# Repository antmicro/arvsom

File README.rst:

=========================================
ARVSOM - Antmicro RISC-V System on Module
=========================================

Copyright (c) 2021 `Antmicro <https://www.antmicro.com>`_

.. image:: https://img.shields.io/badge/View%20on-Antmicro%20Open%20Source%20Portal-332d37?style=flat-square
      :target: https://opensource.antmicro.com/projects/arvsom

.. figure:: img/arvsom.png

Overview
--------

This repository contains open hardware design files for ARVSOM - Antmicro RISC-V System on Module (SoM) based on the StarFive 71x0 SoC.
The design is made in KiCad and currently in progress.

Repository structure
--------------------

The main repository directory contains KiCad PCB project files, a LICENSE and README.
The remaining files are stored in the following directories:

* ``lib`` - contains the component libraries
* ``img`` - contains graphics for this README

Key Features
------------

* StarFive 71x0 SoC (7100 in the current revision until 7110 becomes available)
* 2x DF40 board-to-board connectors for baseboard integration
* HDMI
* Gigabit Ethernet
* USB 3.0
* 2x MIPI CSI-2 (2 lanes each)
* I2C
* MIPI DSI (4 lanes)
* SD/SDIO/eMMC
* 26 GPIOs
* 32MB QSPI NOR Flash memory
* 8GB LPDDR4 (2x 4GB)

License
=======

`Apache-2.0 <LICENSE>`_

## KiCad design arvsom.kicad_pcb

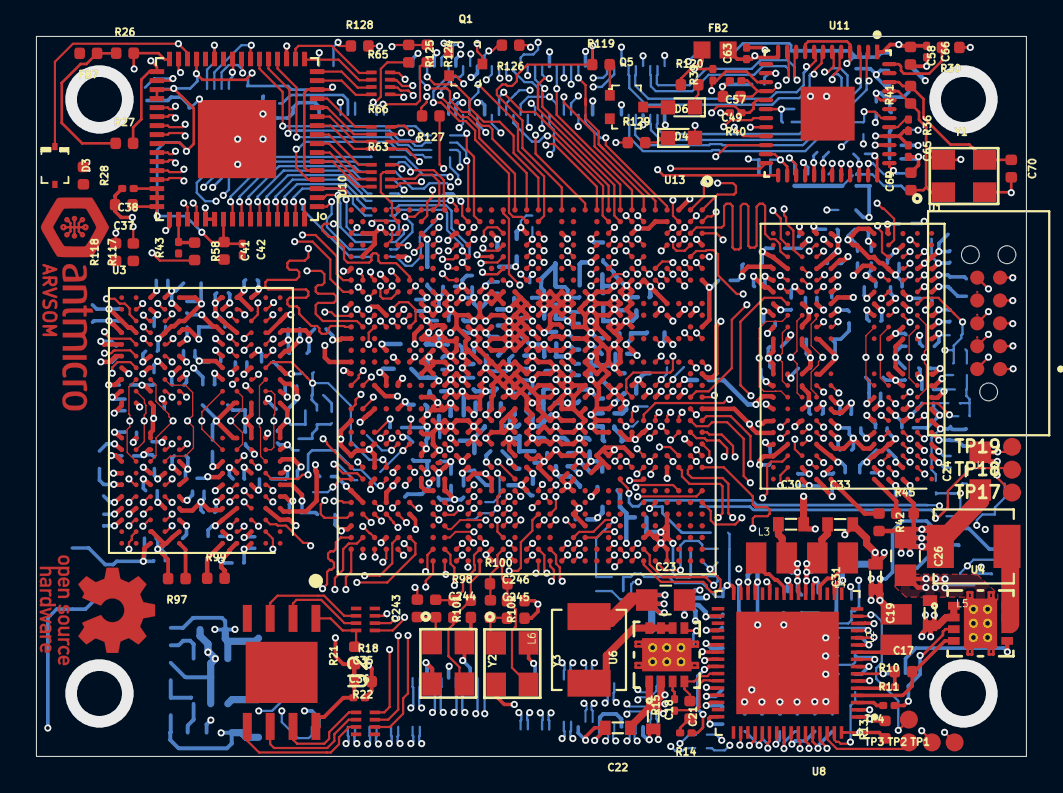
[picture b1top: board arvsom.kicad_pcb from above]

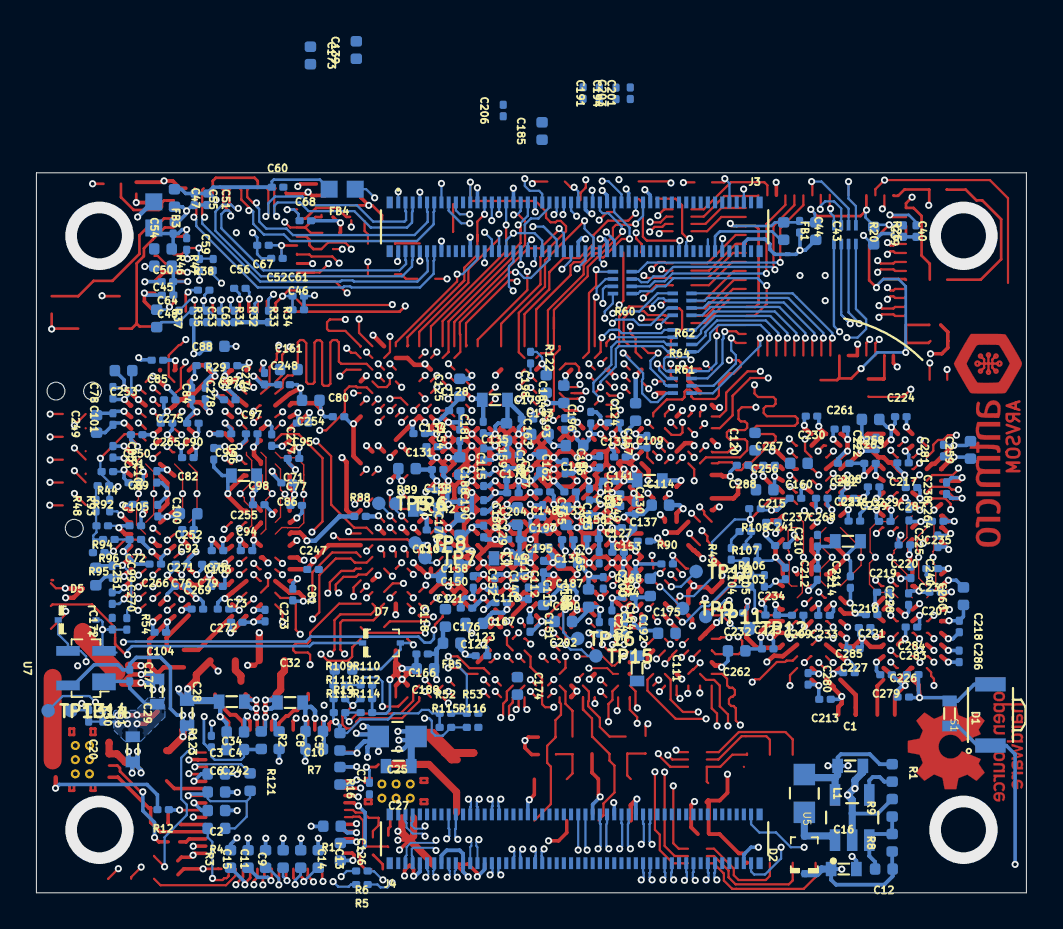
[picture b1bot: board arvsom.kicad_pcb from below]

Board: 12 copper layers, 55.0 x 40.0 mm, 451 parts (349 on the bottom side), 421 nets.

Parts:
C1, C16, C27, C28: C_10u_0603; 0603-cap
C2, C5, C7, C9, C15, C37, C39, C41, C43: C_2u2_0402; 0402-cap
C3, C4, C8, C114, C115, C118, C120, C121, C122, C139, C182, C184, C249, C251, C252, C253, C258, C259, C260, C262: C_10u_0402; 0402-cap
C6, C11, C14, C45, C47, C49, C50, C58: C_4u7_0402; 0402-cap
C10, C13, C17, C18, C242: C_100n_0402_16V; 0402-cap
C12: C_1n0_0402; 0402-cap
C19, C20, C21, C22, C29, C30, C31, C32, C33, C34, C109, C110, C111, C116, C135, C255, C257: C_22u_0603; 0603-cap
C23, C24, C25, C26: C_100u_0805; 0805-cap
C35, C108, C124, C125, C126, C143, C173, C174, C175, C183, C185, C186, C187, C189, C198, C199, C202, C254, C256: C_1u_0402; 0402-cap
C36, C38, C40, C42, C44, C54, C71, C72, C73, C74, C75, C76, C77, C78, C79, C80, C81, C82, C83, C84, C85, C86, C87, C88, C89, C90, C91, C92, C93, C94, C95, C96, C97, C98, C99, C100, C101, C102, C103, C104, C105, C106, C107, C112, C113, C117, C119, C123, C127, C128, C129, C130, C131, C132, C133, C134, C136, C137, C138, C140, C141, C142, C144, C145, C146, C147, C148, C149, C150, C151, C152, C153, C154, C155, C156, C157, C158, C159, C162, C164, C165, C166, C167, C168, C169, C171, C172, C176, C177, C178, C179, C180, C181, C188, C190, C191, C192, C193, C194, C195, C196, C197, C200, C201, C203, C204, C205, C206, C207, C208, C209, C210, C211, C212, C213, C214, C215, C216, C217, C218, C219, C220, C221, C222, C223, C224, C225, C226, C227, C228, C229, C230, C231, C232, C233, C234, C235, C236, C237, C238, C239, C240, C241, C247, C248, C250, C261, C263, C264, C265, C266, C267, C268, C269, C270, C271, C272, C273, C274, C275, C276, C277, C278, C279, C280, C281, C282, C283, C284, C285, C286, C287, C288: C_100n_0201; 0201-res
C46, C48, C51, C52, C53: C_470n_0201; 0201-res
C55, C56, C57, C59, C60, C61, C62, C63, C64, C65, C66, C67, C68: C_10n_0201; 0201-res
C69, C70: C_22p_0402; 0402-cap
C160, C161, C163, C170: C_1n_0402; 0402-res
C243, C244, C245, C246: C_10p_0402; 0402-cap
D1: PGB1010603MR
D2, D3, D5, D7: PMEG3010CEJ; SOD-323F
D4, D6: KP-1608CGCK; LED_0603
FB1, FB5, FB6, FB7: BLM15PD121SN1D; 0402-res
FB2, FB3, FB4: BLM18AG601SN1D; 0603
J1: TAG-10PIN; Tag-Connect_TC2050-IDC-NL
J3, J4: DF40C-100DP-0.4V(51); HRS_DF40C-100DP-0.4V(51)
L1: 10uH; 0805-res
L2, L3, L4: 1uH_2.0x1.6; INDC2016X100N
L5: 0.56uH_7.3A; SRP4020
L6: 0.47uH_10.5A; SRP4020
N1: antmicro_logo; antmicro-logo_scaled_12mm
N2: oshw_logo; oshw-logo
Q1: DMG1013UWQ-7; SOT-323
Q5: DMG1012UW; SOT-323
R1, R98, R100: R_1M0_0402; 0402-res
R2, R3, R4: R_10k_0402; 0402-res
R5, R6, R10, R11, R12, R14, R15, R16, R46, R47, R48, R123: R_0R_0201; 0201-res
R7: R_2k2_0402; 0402-res
R8: R_49k9_0402; 0402-res
R9: R_13k3_0402; 0402-res
R13, R30: R_12k1_0402; 0402-res
R17, R21, R117, R118, R124, R125: R_4k7_0402; 0402-res
R18, R20, R22, R60, R61, R62, R63, R64, R65, R66: 4x33R_0201_array; EXB18V
R19, R26, R27, R29, R37, R120, R121, R129: R_1k_0402; 0402-res
R25, R31, R32, R33, R34, R35, R36, R38, R39, R40, R43, R44, R49, R50, R51, R52, R53, R54, R88, R90, R92, R93, R94, R95, R96, R103, R104, R105, R106, R107, R108, R109, R110, R111, R112, R113, R114, R115, R116, R122: R_10k_0201; 0201-res
R28: R_27k_0402; 0402-res
R41: R_1M5_0402; 0402-res
R42, R45, R89, R91, R97, R99: R_240R_0402; 0402-res
R58, R119, R128: R_33R_0402; 0402-res
R101, R102: R_0R_0402; 0402-res
R126, R127: R_100k_0402; 0402-res
S1: B3U-3000PM; B3U-3000P
TP1, TP2, TP3, TP4, TP17, TP18, TP19: TP_SMD1MM; Testpoint_smd_1mm
TP5, TP6, TP7, TP8, TP9, TP10, TP11, TP12, TP13, TP14, TP15, TP16: TP_SMD_0_75MM; Testpoint_smd_0_75mm
U1, U3: MT53D1024M32D4DT-053; BGA-200_10.0x14.5mm_Layout12x22_P0.80x0.65mm
U2: GD25LQ256DWIGR; GD25Q16CWIG
U4, U6: CSD86330Q3D
U5: LMR62014XMF_NOPB; SOT95P280X145-5N
U7: STM811RW16F; SOT-143-4
U8: TPS65086100; S-PVQFN-N64
U10: TDA19988BHN_C1,557; QFN50P900X900X100-65N
U11: KSZ9031RNXCA; QFN-48-Microchip-QFN77-48LD-PL-2
U13: VIC7100; vic7100
Y1, Y2: ABM8G-25.000MHZ-18-D2Y-T; KX-7
Y3: ABM8G-27.000MHZ-18-D2Y-T; KX-7

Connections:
5V0_IN: J3.77, J3.79, J3.81, J3.83, J3.85, J3.87
/Ethernet/AVDDH: C58.1, C63.1, C66.1, FB2.2, U11.1, U11.12
/Ethernet/AVDDL: C47.1, C51.1, C55.1, C60.1, FB4.2, U11.4, U11.9
/Ethernet/AVDDL_PLL: C50.1, C54.1, C59.1, FB3.2, U11.44
/Ethernet/ETH_RESETn: R46.2, R47.2, U11.42
/PMIC/U5FB: C12.2, R8.2, R9.1, U5.3
/VIC7100 config/ATEMP_TEST0: R51.1, TP13.1, U13.U25
/VIC7100 config/ATEMP_TEST1: R50.1, TP14.1, U13.U24
/VIC7100 config/ATEMP_VCAL: TP16.1, U13.V24
/VIC7100 config/ATEMP_VSS: TP15.1, U13.V25
AVDD3V3_USB: C202.1, C205.1, FB6.1, U13.AA23
AVDD09_PLL: C108.1, C113.1, C119.1, C123.1, FB5.1, U13.U21, U13.U22, U13.V21
BOOT_FROM_UARTn: J3.93, R128.1
BOOT_MODE: R115.2, R116.1, U13.M28
BOOT_SEL0: R109.2, R110.1, U13.E31
BOOT_SEL1: R111.2, R112.1, U13.F31
BOOT_SEL2: Q1.3, R113.2, R114.1, U13.F30
CDTX_DSI_CK_N: J4.69, U13.J30
CDTX_DSI_CK_P: J4.71, U13.J31
CDTX_DSI_D0_N: J4.57, U13.G30
CDTX_DSI_D0_P: J4.59, U13.G31
CDTX_DSI_D1_N: J4.63, U13.H30
CDTX_DSI_D1_P: J4.65, U13.H31
CLK_25M_IN: R98.1, R101.1, U13.Y30
CLK_25M_OUT: C244.1, R98.2, U13.Y31, Y2.3
CLK_27M_IN: R100.1, R102.1, U13.V30
CLK_27M_OUT: C246.1, R100.2, U13.V31, Y3.3
CSI0_PWDN: J3.97, U13.V6
CSI1RX_CLK_N: J4.40, U13.M30
CSI1RX_CLK_P: J4.42, U13.M31
CSI1RX_D0_N: J4.28, U13.P30
CSI1RX_D0_P: J4.30, U13.P31
CSI1RX_D1_N: J4.34, U13.N30
CSI1RX_D1_P: J4.36, U13.N31
CSI2RX_CLK_N: J4.27, U13.U30
CSI2RX_CLK_P: J4.29, U13.U31
CSI2RX_D0_N: J4.15, U13.T30
CSI2RX_D0_P: J4.17, U13.T31
CSI2RX_D1_N: J4.21, U13.R30
CSI2RX_D1_P: J4.23, U13.R31
CTL5: D1.2, J3.92, R4.2, S1.1, U8.63
DDR0_A00: U1.H2, U1.R2, U13.C10
DDR0_A01: U1.J2, U1.P2, U13.B10
DDR0_A02: U1.H9, U1.R9, U13.A15
DDR0_A03: U1.H10, U1.R10, U13.D10
DDR0_A04: U1.H11, U1.R11, U13.D12
DDR0_A05: U1.J11, U1.P11, U13.E10
DDR0_CK0_N: U1.J9, U13.B14
DDR0_CK0_P: U1.J8, U13.A14
DDR0_CK1_N: U1.P9, U13.B12
DDR0_CK1_P: U1.P8, U13.A12
DDR0_CKE0: U1.J4, U1.P4, U13.C17
DDR0_CKE1: U1.J5, U1.P5, U13.F17
DDR0_CS0: U1.H4, U13.F19
DDR0_CS1: U1.H3, U13.A17
DDR0_CS2: U1.R4, U13.B17
DDR0_CS3: U1.R3, U13.E14
DDR0_DMI0: U1.C3, U13.E22
DDR0_DMI1: U1.C10, U13.C19
DDR0_DMI2: U1.Y3, U13.D6
DDR0_DMI3: U1.Y10, U13.D4
DDR0_DQ00: U1.B2, U13.F23
DDR0_DQ01: U1.C2, U13.E23
DDR0_DQ02: U1.E2, U13.D22
DDR0_DQ03: U1.F2, U13.F22
DDR0_DQ04: U1.F4, U13.C22
DDR0_DQ05: U1.E4, U13.B22
DDR0_DQ06: U1.C4, U13.A23
DDR0_DQ07: U1.B4, U13.A22
DDR0_DQ08: U1.B11, U13.A21
DDR0_DQ09: U1.C11, U13.C20
DDR0_DQ10: U1.E11, U13.E20
DDR0_DQ11: U1.F11, U13.D20
DDR0_DQ12: U1.F9, U13.E19
DDR0_DQ13: U1.E9, U13.D19
DDR0_DQ14: U1.C9, U13.B19
DDR0_DQ15: U1.B9, U13.A19
DDR0_DQ16: U1.AA2, U13.A5
DDR0_DQ17: U1.Y2, U13.D7
DDR0_DQ18: U1.V2, U13.C7
DDR0_DQ19: U1.U2, U13.E7
DDR0_DQ20: U1.U4, U13.B5
DDR0_DQ21: U1.V4, U13.C6
DDR0_DQ22: U1.Y4, U13.E6
DDR0_DQ23: U1.AA4, U13.B4
DDR0_DQ24: U1.AA11, U13.A2
DDR0_DQ25: U1.Y11, U13.B3
DDR0_DQ26: U1.V11, U13.A3
DDR0_DQ27: U1.U11, U13.C4
DDR0_DQ28: U1.U9, U13.B2
DDR0_DQ29: U1.V9, U13.B1
DDR0_DQ30: U1.Y9, U13.A1
DDR0_DQ31: U1.AA9, U13.C2
DDR0_DQS0N: U1.E3, U13.C23
DDR0_DQS0P: U1.D3, U13.B23
DDR0_DQS1N: U1.E10, U13.A20
DDR0_DQS1P: U1.D10, U13.B20
DDR0_DQS2N: U1.V3, U13.B6
DDR0_DQS2P: U1.W3, U13.A6
DDR0_DQS3N: U1.V10, U13.C3
DDR0_DQS3P: U1.W10, U13.D3
DDR0_ODT0: R95.1, U1.G2, U13.D17
DDR0_ODT1: R44.2, R92.1, R93.2, U1.T2, U13.G17
DDR0_ODT_0: R48.1, R94.2, R95.2, R96.2
DDR0_ODT_1: R48.2, R92.2
DDR0_PLL_REFOUT_N: TP5.1, U13.D16
DDR0_PLL_REFOUT_P: TP6.1, U13.E16
DDR0_PLL_TESTOUT_N: TP7.1, U13.H19
DDR0_PLL_TESTOUT_P: TP8.1, U13.G19
DDR0_RSTN: U1.T11, U13.B18
DDR1_A00: U3.H2, U3.R2, U13.AG16
DDR1_A01: U3.J2, U3.P2, U13.AJ18
DDR1_A02: U3.H9, U3.R9, U13.AJ16
DDR1_A03: U3.H10, U3.R10, U13.AF14
DDR1_A04: U3.H11, U3.R11, U13.AL14
DDR1_A05: U3.J11, U3.P11, U13.AG14
DDR1_CK0_N: U3.J9, U13.AK18
DDR1_CK0_P: U3.J8, U13.AL18
DDR1_CK1_N: U3.P9, U13.AK16
DDR1_CK1_P: U3.P8, U13.AL16
DDR1_CKE0: U3.J4, U3.P4, U13.AG23
DDR1_CKE1: U3.J5, U3.P5, U13.AJ24
DDR1_CS0: U3.H4, U13.AK23
DDR1_CS1: U3.H3, U13.AH21
DDR1_CS2: U3.R4, U13.AH20
DDR1_CS3: U3.R3, U13.AF20
DDR1_DMI0: U3.C3, U13.AG30
DDR1_DMI1: U3.C10, U13.AJ26
DDR1_DMI2: U3.Y3, U13.AG11
DDR1_DMI3: U3.Y10, U13.AH8
DDR1_DQ00: U3.B2, U13.AF29
DDR1_DQ01: U3.C2, U13.AG29
DDR1_DQ02: U3.E2, U13.AH30
DDR1_DQ03: U3.F2, U13.AF30
DDR1_DQ04: U3.F4, U13.AJ29
DDR1_DQ05: U3.E4, U13.AK29
DDR1_DQ06: U3.C4, U13.AL30
DDR1_DQ07: U3.B4, U13.AL29
DDR1_DQ08: U3.B11, U13.AF26
DDR1_DQ09: U3.C11, U13.AH27
DDR1_DQ10: U3.E11, U13.AG27
DDR1_DQ11: U3.F11, U13.AG26
DDR1_DQ12: U3.F9, U13.AL27
DDR1_DQ13: U3.E9, U13.AL26
DDR1_DQ14: U3.C9, U13.AF24
DDR1_DQ15: U3.B9, U13.AF23
DDR1_DQ16: U3.AA2, U13.AL11
DDR1_DQ17: U3.Y2, U13.AK11
DDR1_DQ18: U3.V2, U13.AL10
DDR1_DQ19: U3.U2, U13.AJ11
DDR1_DQ20: U3.U4, U13.AG10
DDR1_DQ21: U3.V4, U13.AH11
DDR1_DQ22: U3.Y4, U13.AF11
DDR1_DQ23: U3.AA4, U13.AF10
DDR1_DQ24: U3.AA11, U13.AL8
DDR1_DQ25: U3.Y11, U13.AL7
DDR1_DQ26: U3.V11, U13.AK8
DDR1_DQ27: U3.U11, U13.AJ8
DDR1_DQ28: U3.U9, U13.AF8
DDR1_DQ29: U3.V9, U13.AG8
DDR1_DQ30: U3.Y9, U13.AG7
DDR1_DQ31: U3.AA9, U13.AF7
DDR1_DQS0N: U3.E3, U13.AJ30
DDR1_DQS0P: U3.D3, U13.AK30
DDR1_DQS1N: U3.E10, U13.AK27
DDR1_DQS1P: U3.D10, U13.AJ27
DDR1_DQS2N: U3.V3, U13.AJ10
DDR1_DQS2P: U3.W3, U13.AK10
DDR1_DQS3N: U3.V10, U13.AK7
DDR1_DQS3P: U3.W10, U13.AJ7
DDR1_ODT0: R104.1, U3.G2, U13.AH24
DDR1_ODT1: R106.2, R107.1, R108.2, U3.T2, U13.AH23
DDR1_ODT_0: R49.1, R103.2, R104.2, R105.2
DDR1_ODT_1: R49.2, R107.2
DDR1_PLL_REFOUT_N: TP9.1, U13.AF21
DDR1_PLL_REFOUT_P: TP10.1, U13.AG21
DDR1_PLL_TESTOUT_N: TP11.1, U13.AK24
DDR1_PLL_TESTOUT_P: TP12.1, U13.AL24
DDR1_RSTN: U3.T11, U13.AL23
ETH0_N: J3.10, U11.3
ETH0_P: J3.12, U11.2
ETH1_N: J3.6, U11.6
ETH1_P: J3.4, U11.5
ETH2_N: J3.9, U11.8
ETH2_P: J3.11, U11.7
ETH3_N: J3.5, U11.11
ETH3_P: J3.3, U11.10
ETH_LED1: J3.17, R40.1, U11.17
ETH_LED2: J3.15, R39.1, U11.15
GND: C1.2, C2.1, C3.2, C4.2, C5.1, C6.2, C7.1, C8.2, C9.2, C10.2, C11.2, C13.1, C14.1, C15.2, C16.2, C19.2, C20.2, C21.2, C22.2, C23.2, C24.2, C25.2, C26.2, C27.2, C28.2, C29.2, C30.2, C31.2, C32.2, C33.2, C34.2, C35.2, C36.2, C37.2, C38.2, C39.2, C40.2, C41.2, C42.2, C43.2, C44.2, C45.2, C46.2, C47.2, C48.2, C49.2, C50.2, C51.2, C52.2, C53.2, C54.2, C55.2, C56.2, C57.2, C58.2, C59.2, C60.2, C61.2, C62.2, C63.2, C64.2, C65.2, C66.2, C67.2, C68.2, C69.2, C70.2, C71.2, C72.2, C73.2, C74.2, C75.2, C76.2, C77.2, C78.2, C79.2, C80.2, C81.2, C82.2, C83.2, C84.2, C85.2, C86.2, C87.2, C88.2, C89.2, C90.2, C91.2, C92.2, C93.2, C94.2, C95.2, C96.2, C97.2, C98.2, C99.2, C100.2, C101.2, C102.2, C103.2, C104.2, C105.2, C106.2, C107.2, C108.2, C109.2, C110.2, C111.2, C112.2, C113.2, C114.2, C115.2, C116.2, C117.2, C118.2, C119.2, C120.2, C121.2, C122.2, C123.2, C124.2, C125.2, C126.2, C127.2, C128.2, C129.2, C130.2, C131.2, C132.2, C133.2, C134.2, C135.2, C136.2, C137.2, C138.2, C139.2, C140.2, C141.2, C142.2, C143.2, C144.2, C145.2, C146.2, C147.2, C148.2, C149.2, C150.2, C151.2, C152.2, C153.2, C154.2, C155.2, C156.2, C157.2, C158.2, C159.2, C160.2, C161.2, C162.2, C163.2, C164.2, C165.2, C166.2, C167.2, C168.2, C169.2, C170.2, C171.2, C172.2, C173.2, C174.2, C175.2, C176.2, C177.2, C178.2, C179.2, C180.2, C181.2, C182.2, C183.2, C184.2, C185.2, C186.2, C187.2, C188.2, C189.2, C190.2, C191.2, C192.2, C193.2, C194.2, C195.2, C196.2, C197.2, C198.2, C199.2, C200.2, C201.2, C202.2, C203.2, C204.2, C205.2, C206.2, C207.2, C208.2, C209.2, C210.2, C211.2, C212.2, C213.2, C214.2, C215.2, C216.2, C217.2, C218.2, C219.2, C220.2, C221.2, C222.2, C223.2, C224.2, C225.2, C226.2, C227.2, C228.2, C229.2, C230.2, C231.2, C232.2, C233.2, C234.2, C235.2, C236.2, C237.2, C238.2, C239.2, C240.2, C241.2, C242.2, C243.2, C244.2, C245.2, C246.2, C247.2, C248.2, C249.2, C250.2, C251.2, C252.2, C253.2, C254.2, C255.2, C256.2, C257.2, C258.2, C259.2, C260.2, C261.2, C262.2, C263.2, C264.2, C265.2, C266.2, C267.2, C268.2, C269.2, C270.2, C271.2, C272.2, C273.2, C274.2, C275.2, C276.2, C277.2, C278.2, C279.2, C280.2, C281.2, C282.2, C283.2, C284.2, C285.2, C286.2, C287.2, C288.2, D1.1, D6.2, J1.3, J1.5, J1.9, J3.1, J3.2, J3.7, J3.8, J3.13, J3.14, J3.22, J3.23, J3.32, J3.33, J3.42, J3.43, J3.52, J3.53, J3.59, J3.60, J3.65, J3.66, J3.71, J3.74, J3.98, J4.7, J4.8, J4.13, J4.14, J4.19, J4.20, J4.25, J4.26, J4.31, J4.32, J4.37, J4.38, J4.44, J4.50, J4.55, J4.56, J4.61, J4.62, J4.67, J4.68, J4.73, J4.74, J4.79, J4.80, J4.85, J4.86, J4.91, J4.92, J4.97, J4.98, Q5.2, R3.2, R7.2, R9.2, R13.2, R17.2, R25.1, R29.2, R30.1, R50.2, R51.2, R53.2, R89.1, R91.1, R93.1, R96.1, R105.1, R108.1, R110.2, R112.2, R114.2, R116.2, R122.1, S1.2, TP19.1, U1.A3, U1.A10, U1.AB3, U1.AB5, U1.AB8, U1.AB10, U1.C1, U1.C5, U1.C8, U1.C12, U1.D2, U1.D4, U1.D9, U1.D11, U1.E1, U1.E5, U1.E8, U1.E12, U1.G1, U1.G3, U1.G5, U1.G8, U1.G10, U1.G12, U1.J1, U1.J3, U1.J10, U1.J12, U1.K2, U1.K4, U1.K9, U1.K11, U1.N2, U1.N4, U1.N9, U1.N11, U1.P1, U1.P3, U1.P10, U1.P12, U1.T1, U1.T3, U1.T5, U1.T8, U1.T10, U1.T12, U1.V1, U1.V5, U1.V8, U1.V12, U1.W2, U1.W4, U1.W9, U1.W11, U1.Y1, U1.Y5, U1.Y8, U1.Y12, U2.4, U3.A3, U3.A10, U3.AB3, U3.AB5, U3.AB8, U3.AB10, U3.C1, U3.C5, U3.C8, U3.C12, U3.D2, U3.D4, U3.D9, U3.D11, U3.E1, U3.E5, U3.E8, U3.E12, U3.G1, U3.G3, U3.G5, U3.G8, U3.G10, U3.G12, U3.J1, U3.J3, U3.J10, U3.J12, U3.K2, U3.K4, U3.K9, U3.K11, U3.N2, U3.N4, U3.N9, U3.N11, U3.P1, U3.P3, U3.P10, U3.P12, U3.T1, U3.T3, U3.T5, U3.T8, U3.T10, U3.T12, U3.V1, U3.V5, U3.V8, U3.V12, U3.W2, U3.W4, U3.W9, U3.W11, U3.Y1, U3.Y5, U3.Y8, U3.Y12, U4.9, U5.2, U6.9, U7.1, U8.1, U8.6, U8.14, U8.18, U8.29, U8.30, U8.34, U8.36, U8.40, U8.48, U8.50, U8.52, U8.61, U8.65, U10.19, U10.49, U10.53, U10.54, U10.65, U11.29, U11.49, U13.A4, U13.A7, U13.A11, U13.A18, U13.AA8, U13.AA10, U13.AA12, U13.AA13, U13.AA14, U13.AA15, U13.AA17, U13.AA19, U13.AA20, U13.AA22, U13.AA24, U13.AA29, U13.AB3, U13.AB8, U13.AB10, U13.AB11, U13.AB17, U13.AB19, U13.AB20, U13.AB22, U13.AC8, U13.AC9, U13.AC10, U13.AC14, U13.AC15, U13.AC17, U13.AC19, U13.AC20, U13.AC22, U13.AC24, U13.AC25, U13.AD13, U13.AD14, U13.AD15, U13.AD19, U13.AD20, U13.AD21, U13.AD22, U13.AD25, U13.AD28, U13.AD29, U13.AE3, U13.AE8, U13.AE11, U13.AE14, U13.AE15, U13.AE20, U13.AE23, U13.AE24, U13.AE31, U13.AF27, U13.AG5, U13.AG18, U13.AG24, U13.AH3, U13.AH7, U13.AH10, U13.AH13, U13.AH16, U13.AH26, U13.AH29, U13.AJ21, U13.AJ23, U13.AK3, U13.AK5, U13.AK26, U13.AL6, U13.AL9, U13.AL12, U13.AL15, U13.AL19, U13.AL22, U13.AL25, U13.AL28, U13.B21, U13.C1, U13.D2, U13.D9, U13.D23, U13.D27, U13.D28, U13.D29, U13.D30, U13.D31, U13.E2, U13.E17, U13.E29, U13.E30, U13.F7, U13.F16, U13.F20, U13.F24, U13.F29, U13.G3, U13.G13, U13.G16, U13.G20, U13.G22, U13.H7, U13.H9, U13.H10, U13.H16, U13.H17, U13.H18, U13.H20, U13.J9, U13.J10, U13.J12, U13.J16, U13.J17, U13.J22, U13.J23, U13.K3, U13.K5, U13.K8, U13.K9, U13.K10, U13.K11, U13.K22, U13.K23, U13.K25, U13.L8, U13.L9, U13.L10, U13.L11, U13.L12, U13.L13, U13.L16, U13.L18, U13.L19, U13.L20, U13.L22, U13.L23, U13.L28, U13.M10, U13.M11, U13.M12, U13.M13, U13.M14, U13.M15, U13.M16, U13.M17, U13.M18, U13.M20, U13.M22, U13.M24, U13.M25, U13.M26, U13.M27, U13.N3, U13.N12, U13.N15, U13.N16, U13.N17, U13.N18, U13.N20, U13.N22, U13.N24, U13.N25, U13.P12, U13.P14, U13.P15, U13.P18, U13.P20, U13.P22, U13.P24, U13.R12, U13.R14, U13.R15, U13.R20, U13.R22, U13.R23, U13.T3, U13.T9, U13.T10, U13.T11, U13.T12, U13.T14, U13.T22, U13.T24, U13.T25, U13.U8, U13.U9, U13.U10, U13.U11, U13.U12, U13.U13, U13.U18, U13.U19, U13.U20, U13.U23, U13.V10, U13.V11, U13.V12, U13.V13, U13.V18, U13.V19, U13.V20, U13.W3, U13.W10, U13.W12, U13.W13, U13.W20, U13.W21, U13.W24, U13.W25, U13.W30, U13.W31, U13.Y8, U13.Y9, U13.Y10, U13.Y14, U13.Y16, U13.Y17, U13.Y18, U13.Y19, U13.Y20, Y1.2, Y1.4, Y2.2, Y2.4, Y3.2, Y3.4
GP43_LED: J3.21, R119.1, U13.N1
GPIO0: J3.25, U13.E1
GPIO1: J3.24, U13.D1
GPIO2: J3.27, U13.F2
GPIO3: J3.26, U13.G2
GPIO4: J3.29, U13.G6
GPIO5: J3.28, U13.F6
GPIO6: J3.30, U13.F1
GPIO7: J3.31, U13.G1
GPIO8: J3.34, U13.J7
GPIO9: J3.36, U13.G5
GPIO10: J3.35, U13.H2
GPIO11: J3.37, U13.H1
GPIO12: J3.38, U13.F5
GPIO13: J3.51, R126.2, U13.K7
GPIO14: J3.55, U13.J4
GPIO15: J3.39, U13.J3
GPIO16: J3.40, U13.J6
GPIO17: J3.41, U13.F4
GPIO18: J3.44, U13.J2
GPIO19: J3.45, U13.K4
GPIO20: J3.46, U13.G4
GPIO21: J3.47, U13.K6
GPIO22: J3.48, U13.J1
GPIO44: J3.50, U13.R5
GPIO45: J3.49, U13.R4
GPIO46: J3.54, U13.R3
GPIO47: J3.56, U13.R2
GPIO48: J3.58, U13.T7
GPIO55_GMAC_RESETN: R122.2, U13.T4
GPIO63_GMAC_RESETN: R47.1, U13.V7
HDMI_1V8: C37.1, C38.1, C39.1, C40.1, C41.1, C42.1, C43.1, C44.1, FB1.1, U10.5, U10.14, U10.29, U10.35, U10.36, U10.41, U10.46, U10.47, U10.48, U10.55
HDMI_12MHZ: R20.1, U10.27
HDMI_BCLK: R20.2, U10.23
HDMI_CEC: D3.K, J4.51, U10.30
HDMI_DSCL: J4.100, R27.2, U10.33
HDMI_DSDA: J4.99, R26.2, U10.32
HDMI_HPD: J4.53, U10.31
HDMI_I2S_TX0: R20.4, U10.25
HDMI_INT: R43.2, R58.1, U10.50
HDMI_LRCLK: R20.3, U10.24
HDMI_SWING: R25.2, U10.34
HDMI_TX0_N: J4.84, U10.39
HDMI_TX0_P: J4.82, U10.40
HDMI_TX1_N: J4.78, U10.42
HDMI_TX1_P: J4.76, U10.43
HDMI_TX2_N: J4.72, U10.44
HDMI_TX2_P: J4.70, U10.45
HDMI_TXC_N: J4.90, U10.37
HDMI_TXC_P: J4.88, U10.38
I2C0_SCL: R5.1, R117.2, U10.52, U13.W5
I2C0_SDA: R6.1, R118.2, U10.51, U13.V4
I2C2_SCL: J3.80, R124.2, U13.V3
I2C2_SDA: J3.82, R125.2, U13.V5
JTAG_TCK: J1.4, U13.H22
JTAG_TDI: J1.8, U13.C25
JTAG_TDO: J1.6, U13.A25
JTAG_TMS: J1.2, U13.A26
JTAG_TRSTN: J1.10, U13.G23
LCD_DATA0: R61.1, U10.63
LCD_DATA1: R61.2, U10.62
LCD_DATA2: R61.3, U10.61
LCD_DATA3: R61.4, U10.60
LCD_DATA4: R62.1, U10.59
LCD_DATA5: R62.2, U10.58
LCD_DATA6: R62.3, U10.57
LCD_DATA7: R62.4, U10.56
LCD_DATA8: R63.1, U10.9
LCD_DATA9: R63.2, U10.8
LCD_DATA10: R63.3, U10.7
LCD_DATA11: R63.4, U10.6
LCD_DATA12: R64.8, U10.3
LCD_DATA13: R64.7, U10.2
LCD_DATA14: R64.6, U10.1
LCD_DATA15: R64.5, U10.64
LCD_DATA16: R65.1, U10.18
LCD_DATA17: R65.2, U10.17
LCD_DATA18: R65.3, U10.16
LCD_DATA19: R65.4, U10.15
LCD_DATA20: R66.1, U10.13
LCD_DATA21: R66.2, U10.12
LCD_DATA22: R66.3, U10.11
LCD_DATA23: R66.4, U10.10
LCD_DE: R60.2, U10.20
LCD_HSYNC: R60.4, U10.22
LCD_PCLK: R60.1, U10.4
LCD_VSYNC: R60.3, U10.21
LDO_3V3: C6.1, R4.1, R121.2, U8.9
LED_MODE: R36.1, U11.41
unnamed: C11.1, U8.56
unnamed: C13.2, U8.53
unnamed: C14.2, U8.54
unnamed: C17.1, R10.2
unnamed: C17.2, U4.4, U8.4
unnamed: C18.1, R14.2
unnamed: C18.2, U6.4, U8.42
unnamed: C69.1, R41.1, U11.45, Y1.1
unnamed: C70.1, R41.2, U11.46, Y1.3
unnamed: C243.1, R101.2, Y2.1
unnamed: C245.1, R102.2, Y3.1
unnamed: D2.A, L1.2, U5.1
unnamed: D3.A, R28.1
unnamed: D4.1, R120.2
unnamed: D4.2, Q5.3
unnamed: D6.1, R129.2
unnamed: D7.K, TP18.1
unnamed: FB7.1, R26.1, R27.1
unnamed: L2.1, U8.10
unnamed: L3.1, U8.25
unnamed: L4.1, U8.20
unnamed: L5.1, U4.6, U4.7, U4.8
unnamed: L6.1, U6.6, U6.7, U6.8
unnamed: Q1.1, R127.2, R128.2
unnamed: Q5.1, R119.2
unnamed: R1.2, U5.4
unnamed: R5.2, TP1.1, U8.58
unnamed: R6.2, TP2.1, U8.59
unnamed: R10.1, U8.5
unnamed: R11.1, U8.3
unnamed: R11.2, U4.3
unnamed: R12.1, U8.7
unnamed: R12.2, U4.5
unnamed: R13.1, U8.64
unnamed: R14.1, U8.41
unnamed: R15.1, U8.43
unnamed: R15.2, U6.3
unnamed: R16.1, U8.39
unnamed: R16.2, U6.5
unnamed: R17.1, U8.45
unnamed: R18.6, U2.3
unnamed: R18.7, U2.2
unnamed: R18.8, R21.2, U2.1
unnamed: R20.5, U13.M6
unnamed: R20.6, U13.K1
unnamed: R20.7, U13.L1
unnamed: R20.8, U13.H4
unnamed: R22.1, U2.7
unnamed: R22.2, U2.6
unnamed: R22.3, U2.5
unnamed: R30.2, U11.48
unnamed: R42.1, U1.A8
unnamed: R45.1, U1.A5
unnamed: R58.2, U13.M5
unnamed: R60.5, U13.Y2
unnamed: R60.6, U13.AA1
unnamed: R60.7, U13.AA4
unnamed: R60.8, U13.AA3
unnamed: R61.5, U13.AA2
unnamed: R61.6, U13.AB1
unnamed: R61.7, U13.AA6
unnamed: R61.8, U13.AA5
unnamed: R62.5, U13.AB2
unnamed: R62.6, U13.AC1
unnamed: R62.7, U13.AB6
unnamed: R62.8, U13.AB5
unnamed: R63.5, U13.AB4
unnamed: R63.6, U13.AD1
unnamed: R63.7, U13.AG2
unnamed: R63.8, U13.AB7
unnamed: R64.1, U13.AH2
unnamed: R64.2, U13.AG3
unnamed: R64.3, U13.AE1
unnamed: R64.4, U13.AD2
unnamed: R65.5, U13.AE2
unnamed: R65.6, U13.AD3
unnamed: R65.7, U13.AG4
unnamed: R65.8, U13.AL3
unnamed: R66.5, U13.AD5
unnamed: R66.6, U13.AD4
unnamed: R66.7, U13.AH4
unnamed: R66.8, U13.AE4
unnamed: R88.2, U13.C16
unnamed: R89.2, U13.E12
unnamed: R90.2, U13.AJ20
unnamed: R91.2, U13.AG20
unnamed: R97.1, U3.A8
unnamed: R99.1, U3.A5
unnamed: R123.2, U8.27
unnamed: TP3.1, U8.62
unnamed: TP4.1, U8.15
PWR_EN: R121.1, U8.13
QSPI_CLK: R22.7, U13.R25
QSPI_CS0_N: R18.1, U13.P27
QSPI_D0: R22.6, U13.R26
QSPI_D1: R18.2, U13.R27
QSPI_D2: R18.3, U13.P26
QSPI_D3: R22.8, U13.P25
RES_SSRX2_N: J4.6, U13.AC30
RES_SSRX2_P: J4.4, U13.AC31
RES_SSTX2_N: J4.12, U13.AD31
RES_SSTX2_P: J4.10, U13.AD30
RGMII_GTXCLK: U11.24, U13.AA27
RGMII_MDC: R38.1, U11.36, U13.R28
RGMII_MDIO: R37.1, U11.37, U13.Y29
RGMII_RXCLK: R35.1, U11.35, U13.V27
RGMII_RXD0: R31.1, U11.32, U13.P28
RGMII_RXD1: R32.1, U11.31, U13.V28
RGMII_RXD2: R33.1, U11.28, U13.U28
RGMII_RXD3: R34.1, U11.27, U13.V26
RGMII_RXDV: R29.1, U11.33, U13.AA31
RGMII_TXD0: U11.19, U13.AB31
RGMII_TXD1: U11.20, U13.AA26
RGMII_TXD2: U11.21, U13.AA25
RGMII_TXD3: U11.22, U13.V29
RGMII_TXEN: U11.25, U13.AB30
SDIO0_CLK: J3.57, U13.U1
SDIO0_CMD: J3.62, U13.T5
SDIO0_D0: J3.63, U13.T6
SDIO0_D1: J3.67, U13.R1
SDIO0_D2: J3.69, U13.T1
SDIO0_D3: J3.61, U13.T2
SYS_RSTN: C242.1, D5.K, R2.2, R46.1, R123.1, U7.3
TEST_MODE: R52.2, R53.1, U13.M29
UART3_RXD_1V8: TP17.1, U13.H24
UART3_TXD_1V8: D7.A, R19.1, U13.E26
USBD_N: J4.3, U13.AC29
USBD_P: J4.5, U13.AC28
USB_SSRX1_N: J4.18, U13.AD26
USB_SSRX1_P: J4.16, U13.AD27
USB_SSTX1N: J4.24, U13.AC26
USB_SSTX1P: J4.22, U13.AC27
VCC_0V9: C23.1, C25.1, C27.1, C106.1, C111.1, C112.1, C116.1, C118.1, C122.1, C126.1, C129.1, C132.1, C136.1, C140.1, C144.1, C148.1, C152.1, C156.1, C162.1, C164.1, C165.1, C166.1, C167.1, C168.1, C169.1, C170.1, C183.1, C186.1, C189.1, C192.1, C195.1, C197.1, FB5.2, L6.2, U8.44, U8.46, U13.AA11, U13.AA18, U13.AC23, U13.AD23, U13.L17, U13.L21, U13.M19, U13.M21, U13.N19, U13.N21, U13.P16, U13.P17, U13.P19, U13.P21, U13.P23, U13.R16, U13.R17, U13.R18, U13.R19, U13.R21, U13.T15, U13.T16, U13.T17, U13.T18, U13.T19, U13.T20, U13.T21, U13.U14, U13.U15, U13.U16, U13.U17, U13.V14, U13.V15, U13.V16, U13.V17, U13.W11, U13.W14, U13.W15, U13.W16, U13.W17, U13.W18, U13.W19, U13.Y11, U13.Y12, U13.Y13, U13.Y15
VCC_1V1: C24.1, C26.1, C28.1, C71.1, C72.1, C73.1, C74.1, C75.1, C76.1, C77.1, C78.1, C79.1, C80.1, C81.1, C82.1, C83.1, C84.1, C85.1, C86.1, C87.1, C88.1, C89.1, C90.1, C91.1, C92.1, C93.1, C96.1, C98.1, C100.1, C102.1, C103.1, C104.1, C105.1, C107.1, C109.1, C110.1, C114.1, C115.1, C117.1, C120.1, C121.1, C124.1, C125.1, C127.1, C128.1, C130.1, C131.1, C133.1, C134.1, C137.1, C138.1, C141.1, C142.1, C145.1, C146.1, C149.1, C150.1, C153.1, C154.1, C157.1, C158.1, C160.1, C161.1, C207.1, C208.1, C209.1, C210.1, C211.1, C212.1, C213.1, C214.1, C215.1, C216.1, C217.1, C219.1, C220.1, C221.1, C222.1, C224.1, C225.1, C226.1, C227.1, C229.1, C230.1, C231.1, C232.1, C234.1, C235.1, C236.1, C237.1, C239.1, C240.1, C241.1, C248.1, C250.1, C252.1, C253.1, C254.1, C255.1, C256.1, C257.1, C258.1, C259.1, C261.1, C263.1, C269.1, C270.1, C271.1, C272.1, C273.1, C274.1, C275.1, C276.1, C277.1, C278.1, C279.1, C280.1, C281.1, C282.1, C283.1, C284.1, C285.1, C286.1, C287.1, C288.1, L5.2, R42.2, R44.1, R45.2, R88.1, R90.1, R94.1, R97.2, R99.2, R103.1, R106.1, U1.A4, U1.A9, U1.AA3, U1.AA5, U1.AA8, U1.AA10, U1.AB4, U1.AB9, U1.B3, U1.B5, U1.B8, U1.B10, U1.D1, U1.D5, U1.D8, U1.D12, U1.F3, U1.F5, U1.F8, U1.F10, U1.H1, U1.H5, U1.H8, U1.H12, U1.K1, U1.K3, U1.K10, U1.K12, U1.N1, U1.N3, U1.N10, U1.N12, U1.R1, U1.R5, U1.R8, U1.R12, U1.U3, U1.U5, U1.U8, U1.U10, U1.W1, U1.W5, U1.W8, U1.W12, U3.A4, U3.A9, U3.AA3, U3.AA5, U3.AA8, U3.AA10, U3.AB4, U3.AB9, U3.B3, U3.B5, U3.B8, U3.B10, U3.D1, U3.D5, U3.D8, U3.D12, U3.F3, U3.F5, U3.F8, U3.F10, U3.H1, U3.H5, U3.H8, U3.H12, U3.K1, U3.K3, U3.K10, U3.K12, U3.N1, U3.N3, U3.N10, U3.N12, U3.R1, U3.R5, U3.R8, U3.R12, U3.U3, U3.U5, U3.U8, U3.U10, U3.W1, U3.W5, U3.W8, U3.W12, U8.2, U13.AA16, U13.AB12, U13.AB13, U13.AB14, U13.AB15, U13.AB16, U13.AB18, U13.AC11, U13.AC12, U13.AC13, U13.AC16, U13.AC18, U13.AD8, U13.AD9, U13.AD10, U13.AD11, U13.AD12, U13.AD16, U13.AD17, U13.AD18, U13.AE9, U13.AE10, U13.AE12, U13.AE17, U13.AE19, U13.AE21, U13.AE22, U13.G7, U13.G8, U13.G9, U13.G10, U13.G11, U13.H8, U13.H11, U13.H12, U13.H13, U13.H14, U13.H15, U13.J11, U13.J13, U13.J14, U13.J15, U13.J18, U13.J19, U13.J20, U13.K12, U13.K13, U13.K14, U13.K15, U13.K16, U13.K17, U13.K18, U13.K19, U13.L14, U13.L15
VCC_1V2: C33.1, C34.1, C45.1, C46.1, C48.1, C52.1, C56.1, C61.1, C64.1, C67.1, C68.1, FB3.1, FB4.1, L4.2, U8.22, U11.14, U11.18, U11.23, U11.26, U11.30, U11.39
VCC_1V8: C5.2, C30.1, C32.1, C35.1, C36.1, C94.1, C95.1, C97.1, C99.1, C101.1, C135.1, C139.1, C143.1, C147.1, C151.1, C155.1, C159.1, C163.1, C173.1, C174.1, C175.1, C176.1, C177.1, C178.1, C179.1, C180.1, C181.1, C218.1, C223.1, C228.1, C233.1, C238.1, C247.1, C249.1, C251.1, C260.1, C262.1, C264.1, C265.1, C266.1, C267.1, C268.1, FB1.2, J1.1, J3.88, J3.90, L3.2, Q1.2, R2.1, R19.2, R21.1, R52.1, R54.1, R109.1, R111.1, R113.1, R115.1, R127.1, U1.F1, U1.F12, U1.G4, U1.G9, U1.T4, U1.T9, U1.U1, U1.U12, U2.8, U3.F1, U3.F12, U3.G4, U3.G9, U3.T4, U3.T9, U3.U1, U3.U12, U8.23, U8.32, U13.AB21, U13.AD24, U13.M8, U13.M9, U13.M23, U13.N8, U13.N9, U13.N10, U13.N11, U13.P8, U13.P9, U13.P10, U13.P11, U13.R8, U13.R9, U13.R10, U13.R11, U13.T23, U13.W23
VCC_3V3: C29.1, C31.1, C49.1, C53.1, C57.1, C62.1, C65.1, C171.1, C182.1, C184.1, C185.1, C187.1, C188.1, C190.1, C191.1, C193.1, C194.1, C196.1, C198.1, C199.1, C200.1, C201.1, C203.1, C204.1, C206.1, FB2.1, FB6.2, J3.84, J3.86, L2.2, R28.2, R31.2, R32.2, R33.2, R34.2, R35.2, R36.2, R37.2, R38.2, R39.2, R40.2, R43.1, R117.1, R118.1, R120.1, R124.1, R125.1, R126.1, R129.1, U7.4, U8.12, U11.16, U11.34, U11.40, U13.AA9, U13.AA21, U13.AB9, U13.N13, U13.N14, U13.P13, U13.R13, U13.T13, U13.V8, U13.V9, U13.W8, U13.W9, U13.Y21
VCC_5V0: C1.1, C2.2, C3.1, C4.1, C7.2, C8.1, C15.1, C19.1, C20.1, C21.1, C22.1, FB7.2, L1.1, R1.1, U4.1, U4.2, U5.5, U6.1, U6.2, U8.8, U8.11, U8.21, U8.24, U8.38, U8.57
VDD2PEN: R3.1, U8.60, U13.V1
VDD2PEN_OTP_1V8: C10.1, R7.1, U8.31, U13.AC21
VIC_RSTN: C172.1, D5.A, R54.2, U7.2, U13.L29
VSYS_5V8: C9.1, C12.1, C16.1, D2.K, R8.1, U8.55
